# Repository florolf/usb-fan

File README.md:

# usb-fan

Little PCB to power and control a 5V PWM fan (like
[this one](https://noctua.at/de/nf-a20-5v-pwm)) through a USB-C port.

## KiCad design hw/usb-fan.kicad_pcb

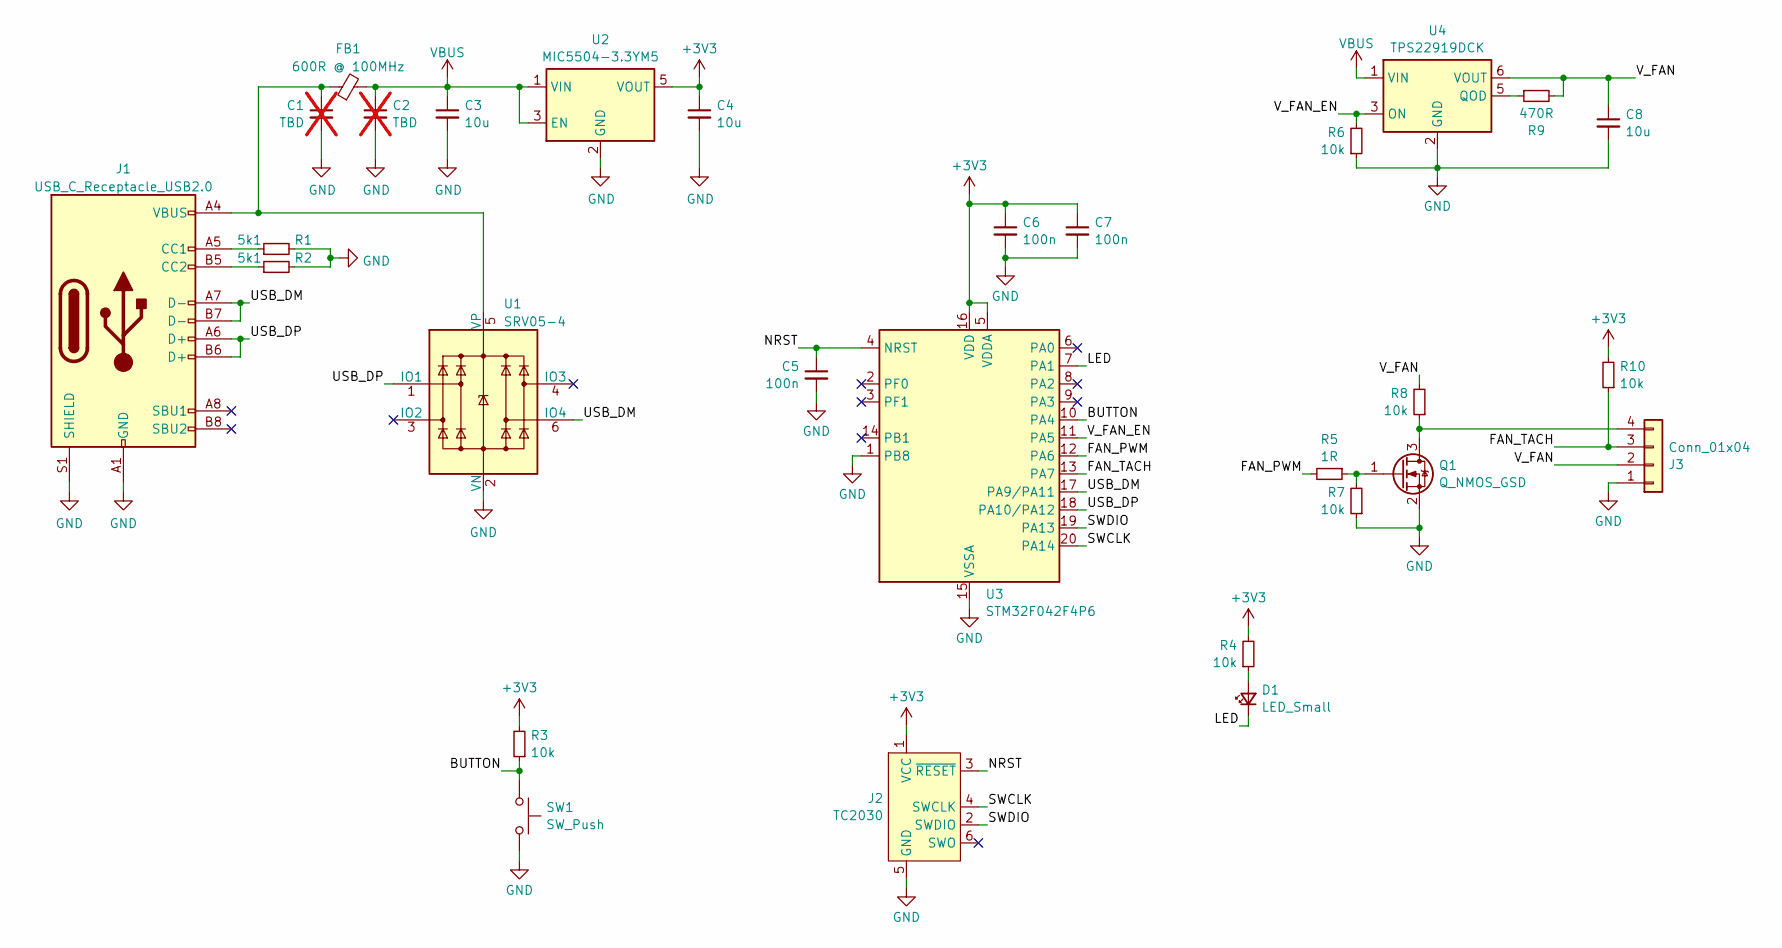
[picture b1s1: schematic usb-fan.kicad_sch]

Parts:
C1: TBD; C_0402_1005Metric; not fitted
C2: TBD; C_0402_1005Metric; MPN CL05B104KB54PNC; not fitted
C3, C4, C8: 10u; C_0805_2012Metric; MPN CL21A106KOQNNNE; Digikey 1276-1096-1-ND
C5, C6, C7: 100n; C_0402_1005Metric
D1: LED_Small; LED_0603_1608Metric
FB1: 600R @ 100MHz; L_0805_2012Metric; MPN BBPY00201209601Y00; Digikey 553-BBPY00201209601Y00CT-ND
J1: USB_C_Receptacle_USB2.0; USB_C_Receptacle_HRO_TYPE-C-31-M-12; MPN TYPE-C-31-M-12
J2: TC2030; Tag-Connect_TC2030-IDC-NL_2x03_P1.27mm_Vertical
J3: Conn_01x04; FanPinHeader_1x04_P2.54mm_Vertical; MPN 0470531000; Digikey WM4330-ND
Q1: Q_NMOS_GSD; SOT-323_SC-70; MPN BSS816NWH6327XTSA1; Digikey BSS816NWH6327XTSA1CT-ND
R1, R2: 5k1; R_0402_1005Metric; MPN 0402WGF5101TCE
R3, R4, R6, R7, R8, R10: 10k; R_0402_1005Metric
R5: 1R; R_0402_1005Metric
R9: 470R; R_0603_1608Metric
SW1: SW_Push; SW_SPST_B3S-1000; MPN B3S-1000; Digikey SW415-ND
U1: SRV05-4; SOT-23-6
U2: MIC5504-3.3YM5; SOT-23-5
U3: STM32F042F4P6; TSSOP-20_4.4x6.5mm_P0.65mm; MPN STM32F042F4P6; Digikey 497-17343-ND
U4: TPS22919DCK; SOT-363_SC-70-6; MPN TPS22919DCK; Digikey 296-TPS22919DCKRCT-ND

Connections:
+3V3: C4.1, C6.1, C7.1, J2.1 (VCC), R3.2, R4.2, R10.2, U2.5 (VOUT), U3.5 (VDDA), U3.16 (VDD)
/BUTTON: R3.1, SW1.1, U3.10 (PA4)
/FAN_PWM: R5.2, U3.12 (PA6)
/FAN_TACH: J3.3, R10.1, U3.13 (PA7)
/LED: D1.1 (K), U3.7 (PA1)
/NRST: C5.1, J2.3 (~RESET), U3.4 (NRST)
/SWCLK: J2.4 (SWCLK), U3.20 (PA14)
/SWDIO: J2.2 (SWDIO), U3.19 (PA13)
/USB_DM: J1.A7 (D-), J1.B7 (D-), U1.6 (IO4), U3.17 (PA9/PA11)
/USB_DP: J1.A6 (D+), J1.B6 (D+), U1.1 (IO1), U3.18 (PA10/PA12)
/V_FAN: C8.1, J3.2, R8.2, R9.2, U4.6 (VOUT)
/V_FAN_EN: R6.2, U3.11 (PA5), U4.3 (ON)
GND: C1.2, C2.2, C3.2, C4.2, C5.2, C6.2, C7.2, C8.2, J1.A1 (GND), J1.A12 (GND), J1.B1 (GND), J1.B12 (GND), J1.S1 (SHIELD), J2.5 (GND), J3.1, Q1.2 (S), R1.2, R2.2, R6.1, R7.1, SW1.2, U1.2 (VN), U2.2 (GND), U3.1 (PB8), U3.15 (VSSA), U4.2 (GND)
unnamed: D1.2 (A), R4.1
unnamed: J1.A5 (CC1), R1.1
unnamed: J1.B5 (CC2), R2.1
unnamed: J3.4, Q1.3 (D), R8.1
unnamed: Q1.1 (G), R5.1, R7.2
unnamed: C1.1, FB1.1, J1.A4 (VBUS), J1.A9 (VBUS), J1.B4 (VBUS), J1.B9 (VBUS), U1.5 (VP)
unnamed: R9.1, U4.5 (QOD)
VBUS: C2.1, C3.1, FB1.2, U2.1 (VIN), U2.3 (EN), U4.1 (VIN)

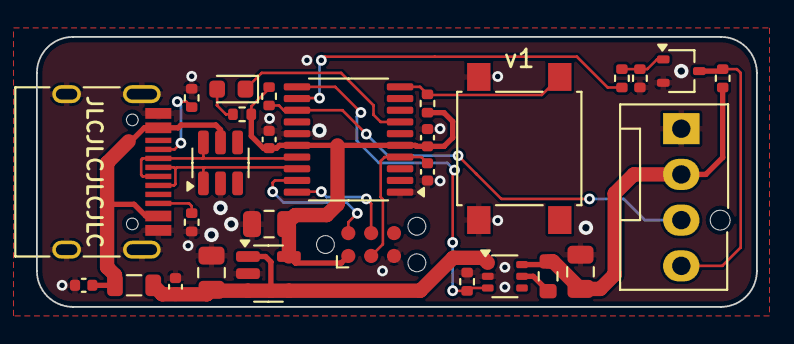
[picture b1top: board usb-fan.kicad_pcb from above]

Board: 2 copper layers, 40.0 x 15.0 mm, 29 parts (0 on the bottom side), 21 nets.

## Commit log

2025-06-19 import
